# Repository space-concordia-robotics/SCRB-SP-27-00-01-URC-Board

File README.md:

# SCRB-SP-27-00-01
Science Payload URC Extension Board

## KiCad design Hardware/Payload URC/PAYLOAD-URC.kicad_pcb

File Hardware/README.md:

Hardware design for Science Payload URC Extension board

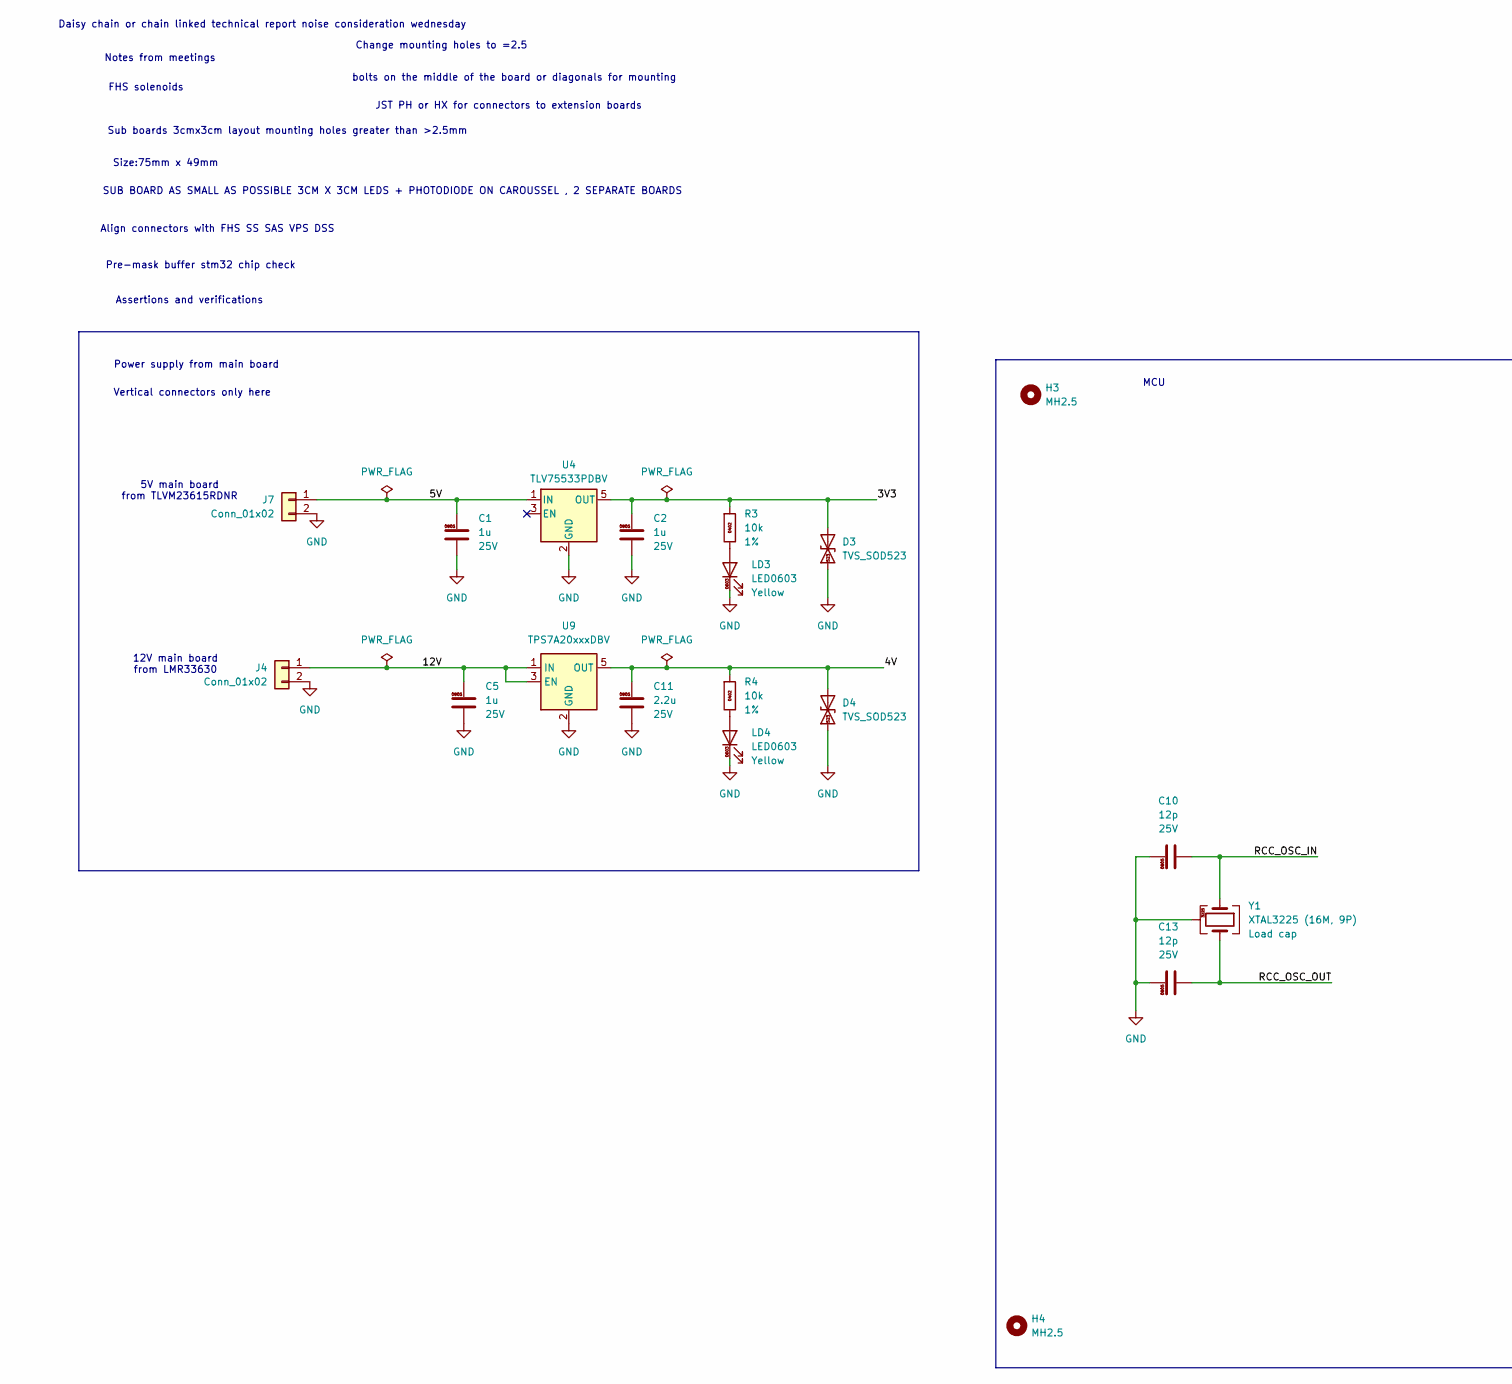
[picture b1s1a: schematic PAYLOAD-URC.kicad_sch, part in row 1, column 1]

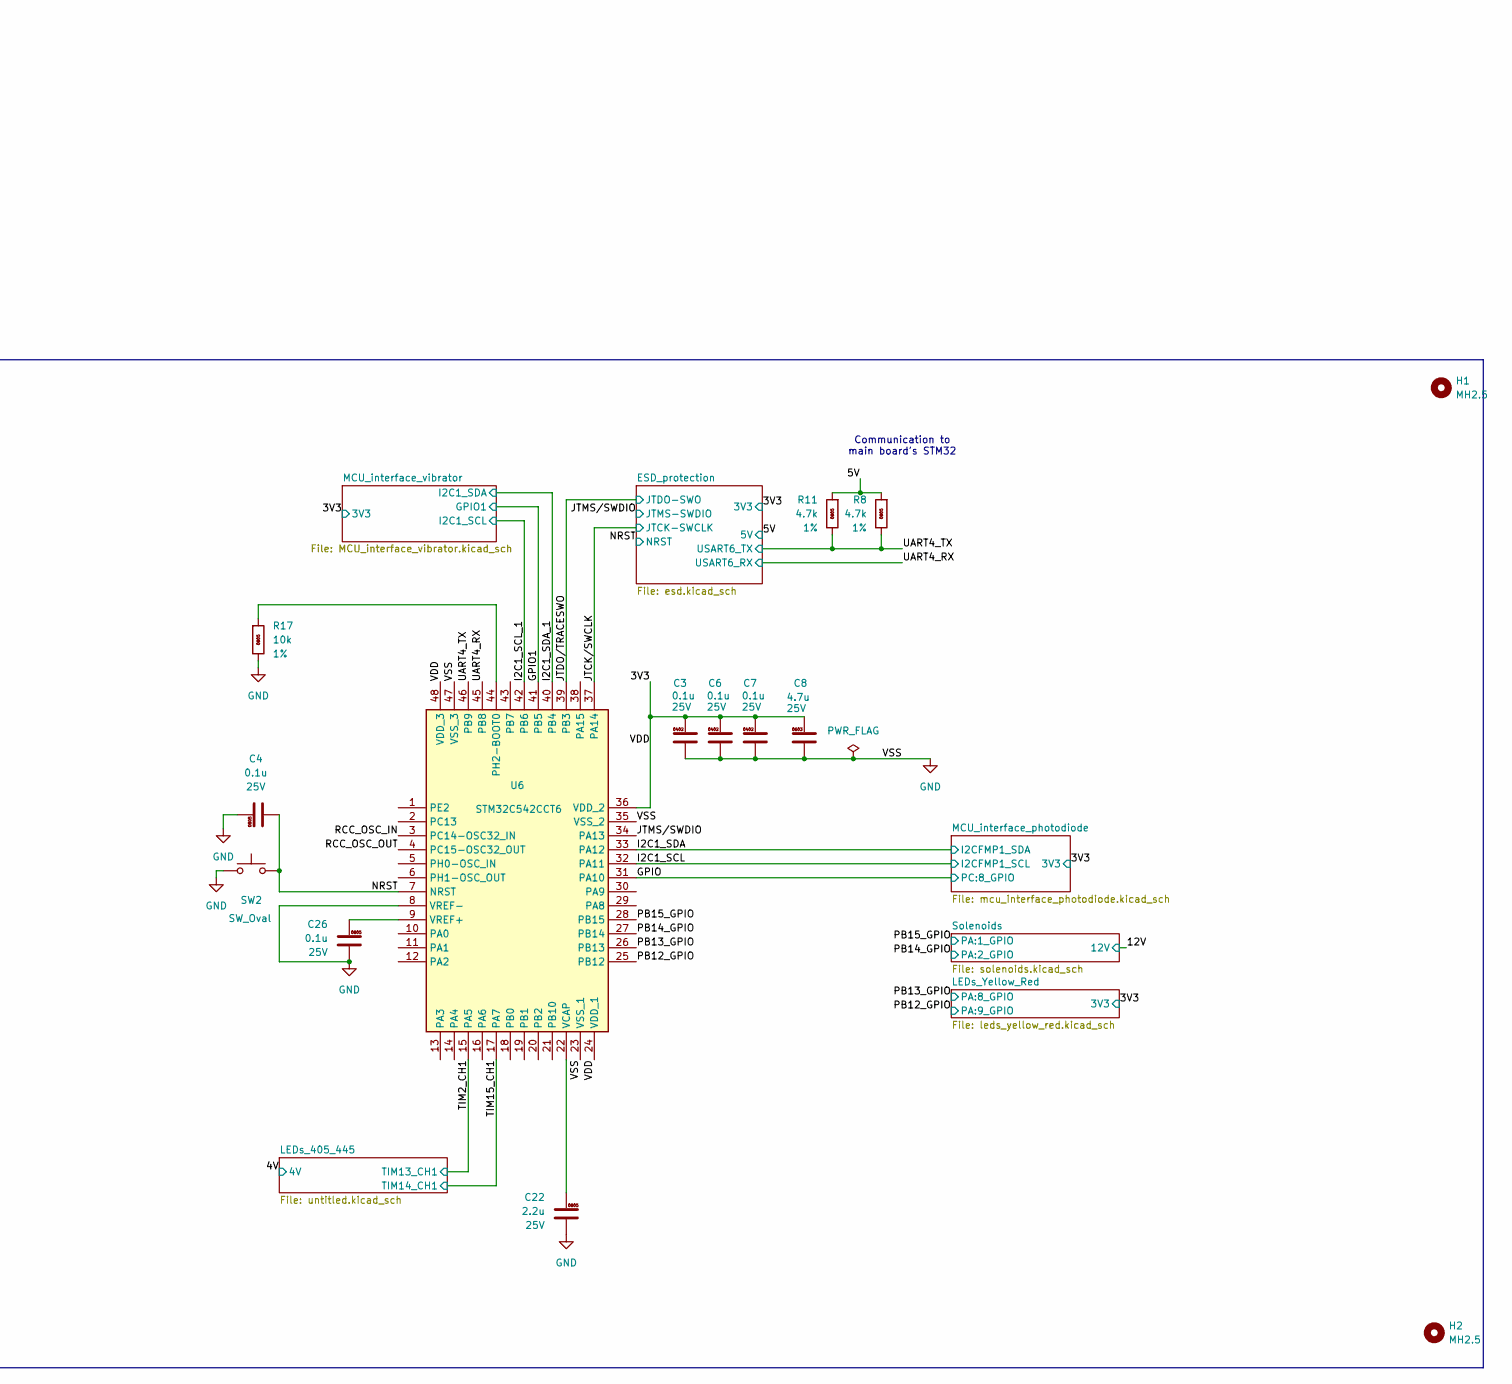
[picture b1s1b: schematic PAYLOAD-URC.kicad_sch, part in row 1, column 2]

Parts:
C1, C2, C5: 1u; C0805; Voltage 25V
C3, C6, C7: 0.1u; C0402; Voltage 25V
C4, C26: 0.1u; C0805; Voltage 25V
C8: 4.7u; C0603; Voltage 25V
C10, C13: 12p; C0805; Voltage 25V
C11, C22: 2.2u; C0805; Voltage 25V
D3, D4: TVS_SOD523; SOD-523
H1, H2, H3, H4: MH2.5; MountingHole_3mm_Pad_TopBottom
J4, J7: Conn_01x02; Molex_Micro-Fit_3.0_43650-0215_1x02_P3.00mm_Vertical
LD3, LD4: LED0603
R3, R4: 10k; R0402
R8, R11: 4.7k; R0805
R17: 10k; R0805
SW2: SW_Oval; SW_C2888430
U4: TLV75533PDBV; SOT-23-5
U6: STM32C542CCT6; LQFP-48_7x7mm_P0.5mm; Manufacturer_Part_Number STM32C542CCT6
U9: TPS7A20xxxDBV; SOT-23-5
Y1: XTAL3225 (16M, 9P); SMD3225

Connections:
/3V3: C2.1, C3.1, C6.1, C7.1, C8.1, D3.2 (A2), R3.1, U4.5 (OUT), U6.24 (VDD_1), U6.36 (VDD_2), U6.48 (VDD_3); also elsewhere on the board
/4V: C11.1, D4.2 (A2), R4.1, U9.5 (OUT); also elsewhere on the board
/5V: C1.1, J7.1, R8.1, R11.1, U4.1 (IN); also elsewhere on the board
/12V: C5.1, J4.1, U9.1 (IN), U9.3 (EN); also elsewhere on the board
/GPIO: U6.31 (PA10); also elsewhere on the board
/GPIO1: U6.41 (PB5)
/I2C1_SCL: U6.32 (PA11); also elsewhere on the board
/I2C1_SCL_1: U6.42 (PB6); also elsewhere on the board
/I2C1_SDA: U6.33 (PA12); also elsewhere on the board
/I2C1_SDA_1: U6.40 (PB4); also elsewhere on the board
/JTCK/SWCLK: U6.37 (PA14); also elsewhere on the board
/JTDO/TRACESWO: U6.39 (PB3)
/JTMS/SWDIO: U6.34 (PA13); also elsewhere on the board
/NRST: C4.2, SW2.2, U6.7 (NRST)
/PB12_GPIO: U6.25 (PB12); also elsewhere on the board
/PB13_GPIO: U6.26 (PB13); also elsewhere on the board
/PB14_GPIO: U6.27 (PB14); also elsewhere on the board
/PB15_GPIO: U6.28 (PB15); also elsewhere on the board
/RCC_OSC_IN: C10.2, U6.3 (PC14-OSC32_IN), Y1.1
/RCC_OSC_OUT: C13.2, U6.4 (PC15-OSC32_OUT), Y1.3
/TIM2_CH1: U6.15 (PA5); also elsewhere on the board
/TIM15_CH1: U6.17 (PA7); also elsewhere on the board
/UART4_RX: U6.45 (PB8); also elsewhere on the board
/UART4_TX: R8.2, R11.2, U6.46 (PB9); also elsewhere on the board
GND: C1.2, C2.2, C3.2, C4.1, C5.2, C6.2, C7.2, C8.2, C10.1, C11.2, C13.1, C22.2, C26.2, D3.1 (A1), D4.1 (A1), J4.2, J7.2, LD3.1 (K), LD4.1 (K), R17.2, SW2.1, U4.2 (GND), U6.8 (VREF-), U6.23 (VSS_1), U6.35 (VSS_2), U6.47 (VSS_3), U9.2 (GND), Y1.2, Y1.4; also elsewhere on the board
unnamed: LD3.2 (A), R3.2
unnamed: LD4.2 (A), R4.2
unnamed: R17.1, U6.44 (PH2-BOOT0)
unnamed: C22.1, U6.22 (VCAP)
unnamed: C26.1, U6.9 (VREF+)

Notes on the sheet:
12V main board from LMR33630
Assertions and verifications
Change mounting holes to =2.5
Communication to main board's STM32
FHS solenoids
Size:75mm x 49mm
Notes from meetings
JST PH or HX for connectors to extension boards
Daisy chain or chain linked technical report noise consideration wednesday
Power supply from main board
SUB BOARD AS SMALL AS POSSIBLE 3CM X 3CM LEDS + PHOTODIODE ON CAROUSSEL , 2 SEPARATE BOARDS
bolts on the middle of the board or diagonals for mounting
Align connectors with FHS SS SAS VPS DSS
Sub boards 3cmx3cm layout mounting holes greater than >2.5mm
MCU
Pre-mask buffer stm32 chip check
5V main board from TLVM23615RDNR
Vertical connectors only here

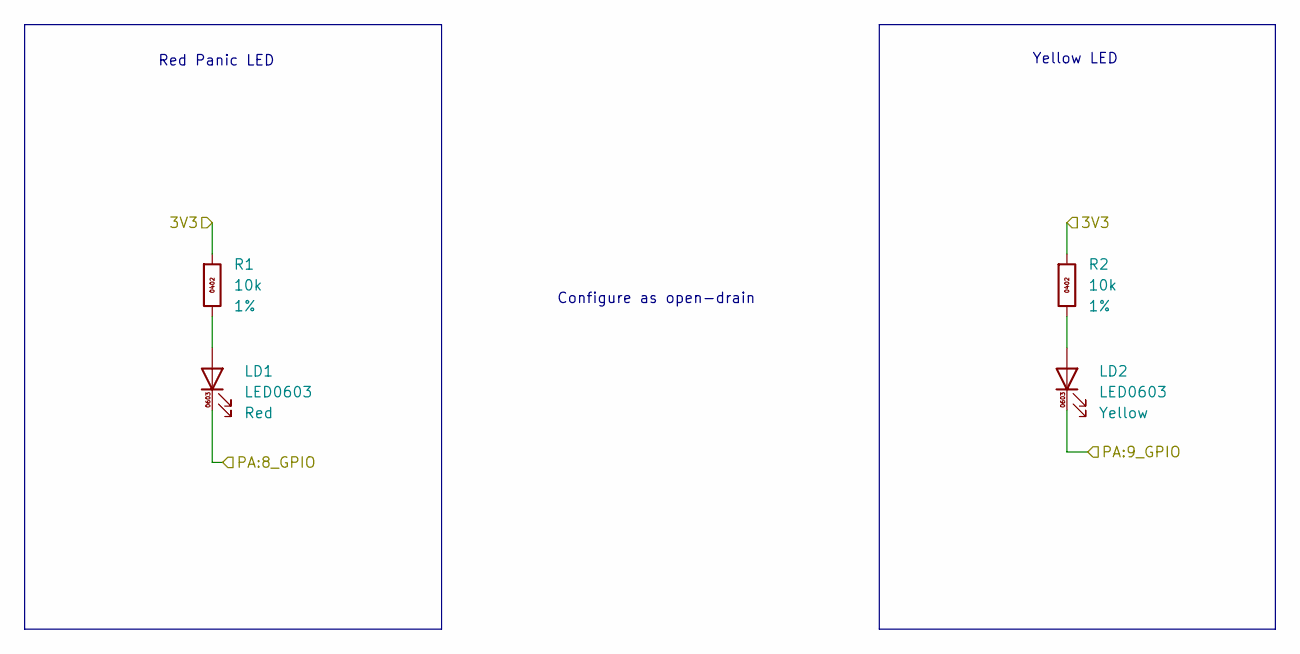
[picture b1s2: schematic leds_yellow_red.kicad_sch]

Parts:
LD1, LD2: LED0603
R1, R2: 10k; R0402

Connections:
/3V3: R1.1, R2.1; also elsewhere on the board
/PB12_GPIO: LD2.1 (K); also elsewhere on the board
/PB13_GPIO: LD1.1 (K); also elsewhere on the board
unnamed: LD1.2 (A), R1.2
unnamed: LD2.2 (A), R2.2

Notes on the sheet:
Red Panic LED
Configure as open-drain
Yellow LED

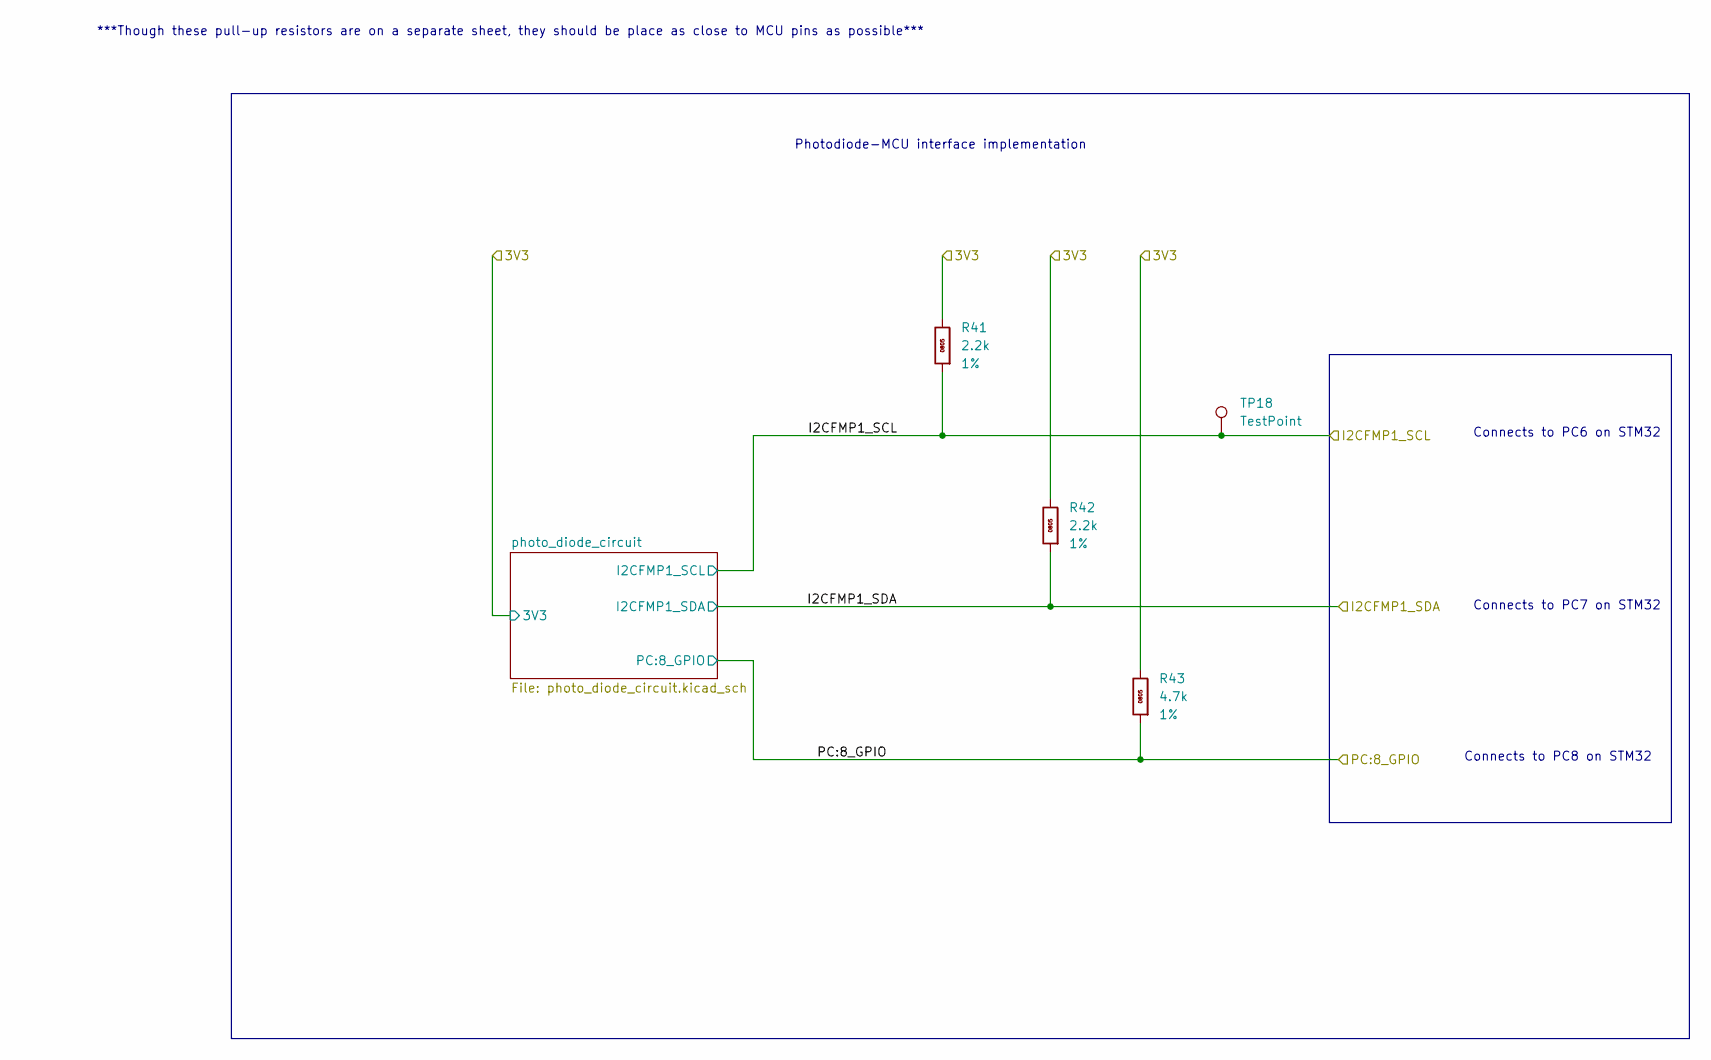
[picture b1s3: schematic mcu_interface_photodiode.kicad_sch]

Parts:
R41, R42: 2.2k; R0805
R43: 4.7k; R0805
TP18: TestPoint; TestPoint_Loop_D2.60mm_Drill1.6mm_Beaded

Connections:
/3V3: R41.2, R42.2, R43.2; also elsewhere on the board
/GPIO: R43.1; also elsewhere on the board
/I2C1_SCL: R41.1, TP18.1 (1_1); also elsewhere on the board
/I2C1_SDA: R42.1; also elsewhere on the board

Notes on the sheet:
***Though these pull-up resistors are on a separate sheet, they should be place as close to MCU pins as possible***
Photodiode-MCU interface implementation
Connects to PC7 on STM32
Connects to PC6 on STM32
Connects to PC8 on STM32

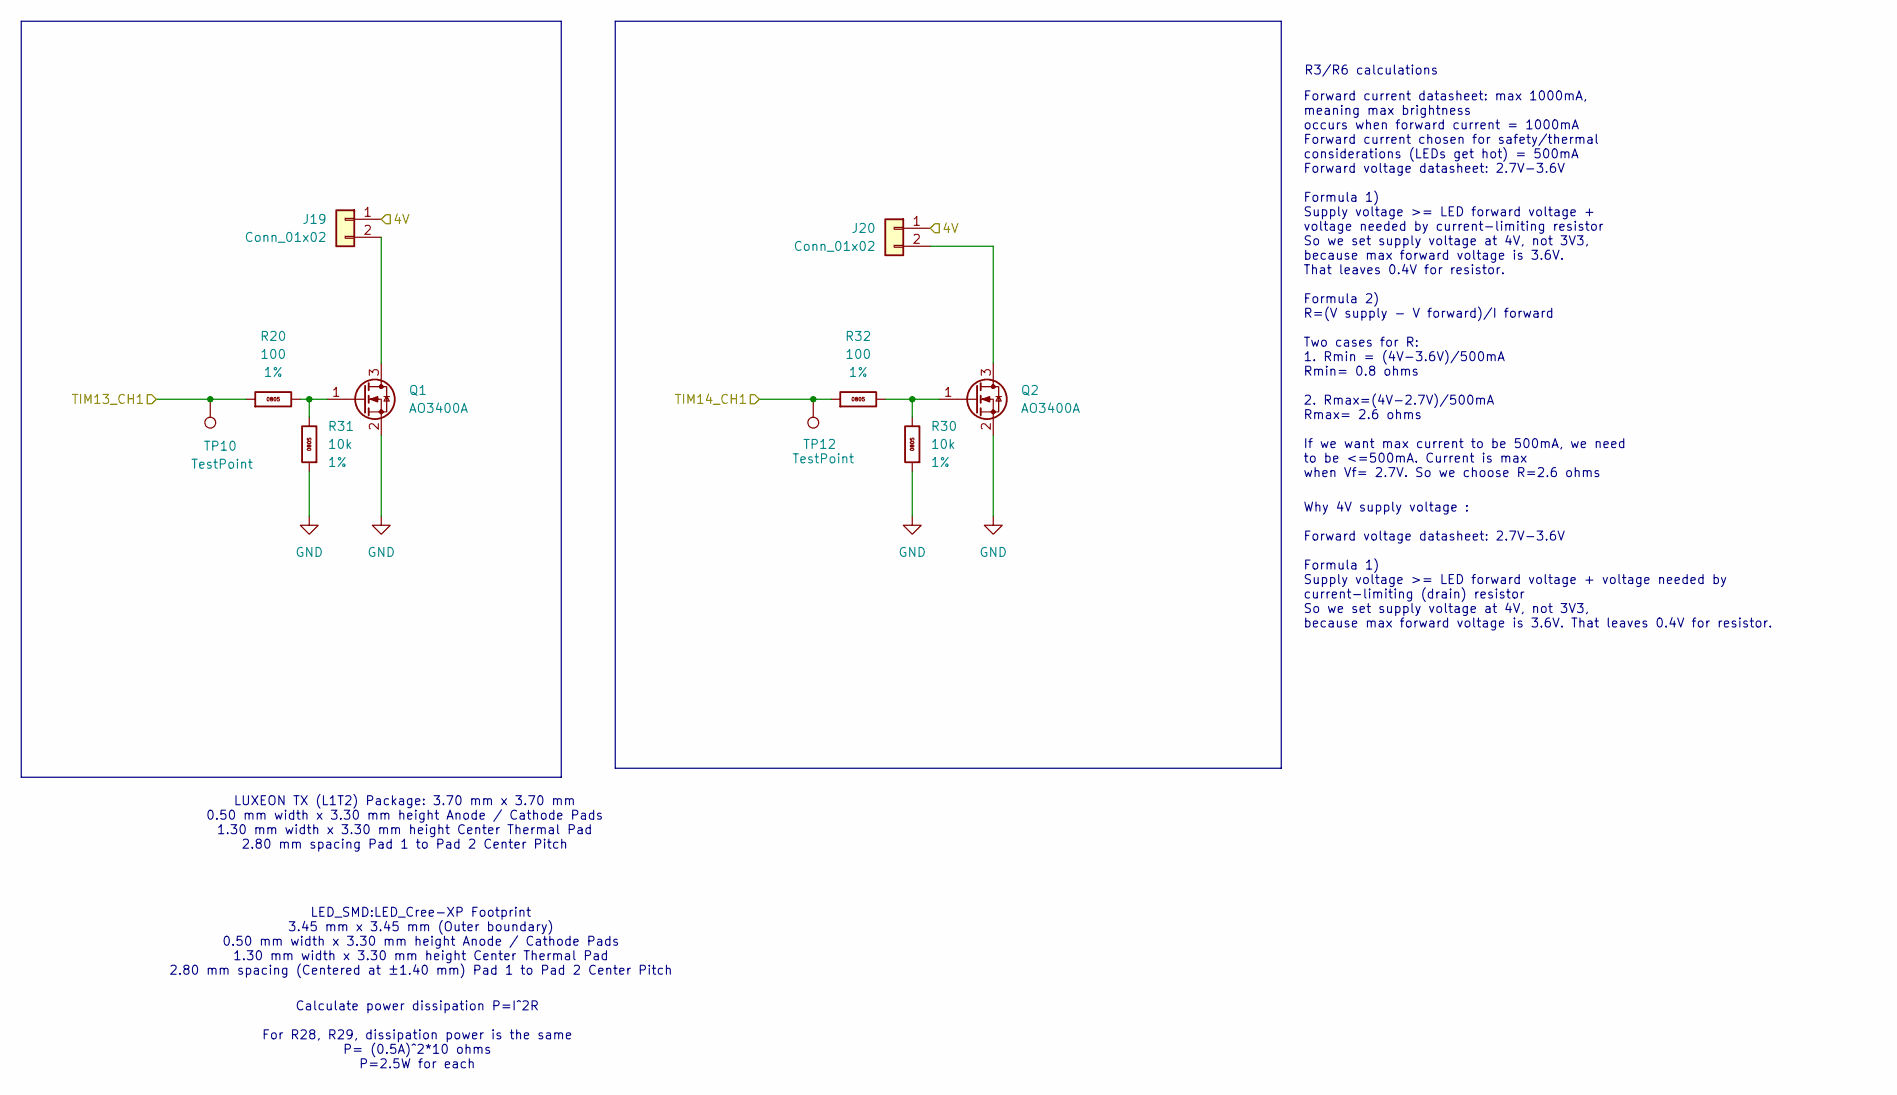
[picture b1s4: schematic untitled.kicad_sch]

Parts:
J19, J20: Conn_01x02; JST-GH-SM04B-GHS-TB
Q1, Q2: AO3400A; SOT-23
R20, R32: 100; R0805
R30, R31: 10k; R0805
TP10, TP12: TestPoint; TestPoint_Loop_D2.60mm_Drill1.6mm_Beaded

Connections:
/4V: J19.1, J20.1; also elsewhere on the board
/TIM2_CH1: R20.1, TP10.1 (1_1); also elsewhere on the board
/TIM15_CH1: R32.1, TP12.1 (1_1); also elsewhere on the board
GND: Q1.2 (S), Q2.2 (S), R30.1, R31.1; also elsewhere on the board
unnamed: J19.2, Q1.3 (D)
unnamed: J20.2, Q2.3 (D)
unnamed: Q1.1 (G), R20.2, R31.2
unnamed: Q2.1 (G), R30.2, R32.2

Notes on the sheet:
LUXEON TX (L1T2) Package: 3.70 mm x 3.70 mm 0.50 mm width x 3.30 mm height Anode / Cathode Pads 1.30 mm width x 3.30 mm height Center Thermal Pad 2.80 mm spacing Pad 1 to Pad 2 Center Pitch
R3/R6 calculations
LED_SMD:LED_Cree-XP Footprint 3.45 mm x 3.45 mm (Outer boundary) 0.50 mm width x 3.30 mm height Anode / Cathode Pads 1.30 mm width x 3.30 mm height Center Thermal Pad 2.80 mm spacing (Centered at ±1.40 mm) Pad 1 to Pad 2 Center Pitch
Forward current datasheet: max 1000mA, meaning max brightness occurs when forward current = 1000mA Forward current chosen for safety/thermal considerations (LEDs get hot) = 500mA Forward voltage datasheet: 2.7V-3.6V Formula 1) Supply voltage >= LED forward voltage + voltage needed by current-limiti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
Why 4V supply voltage : Forward voltage datasheet: 2.7V-3.6V Formula 1) Supply voltage >= LED forward voltage + voltage needed by current-limiting (drain) resistor So we set supply voltage at 4V, not 3V3, because max forward voltage is 3.6V. That leaves 0.4V for resistor.
Calculate power dissipation P=I^2R For R28, R29, dissipation power is the same P= (0.5A)^2*10 ohms P=2.5W for each

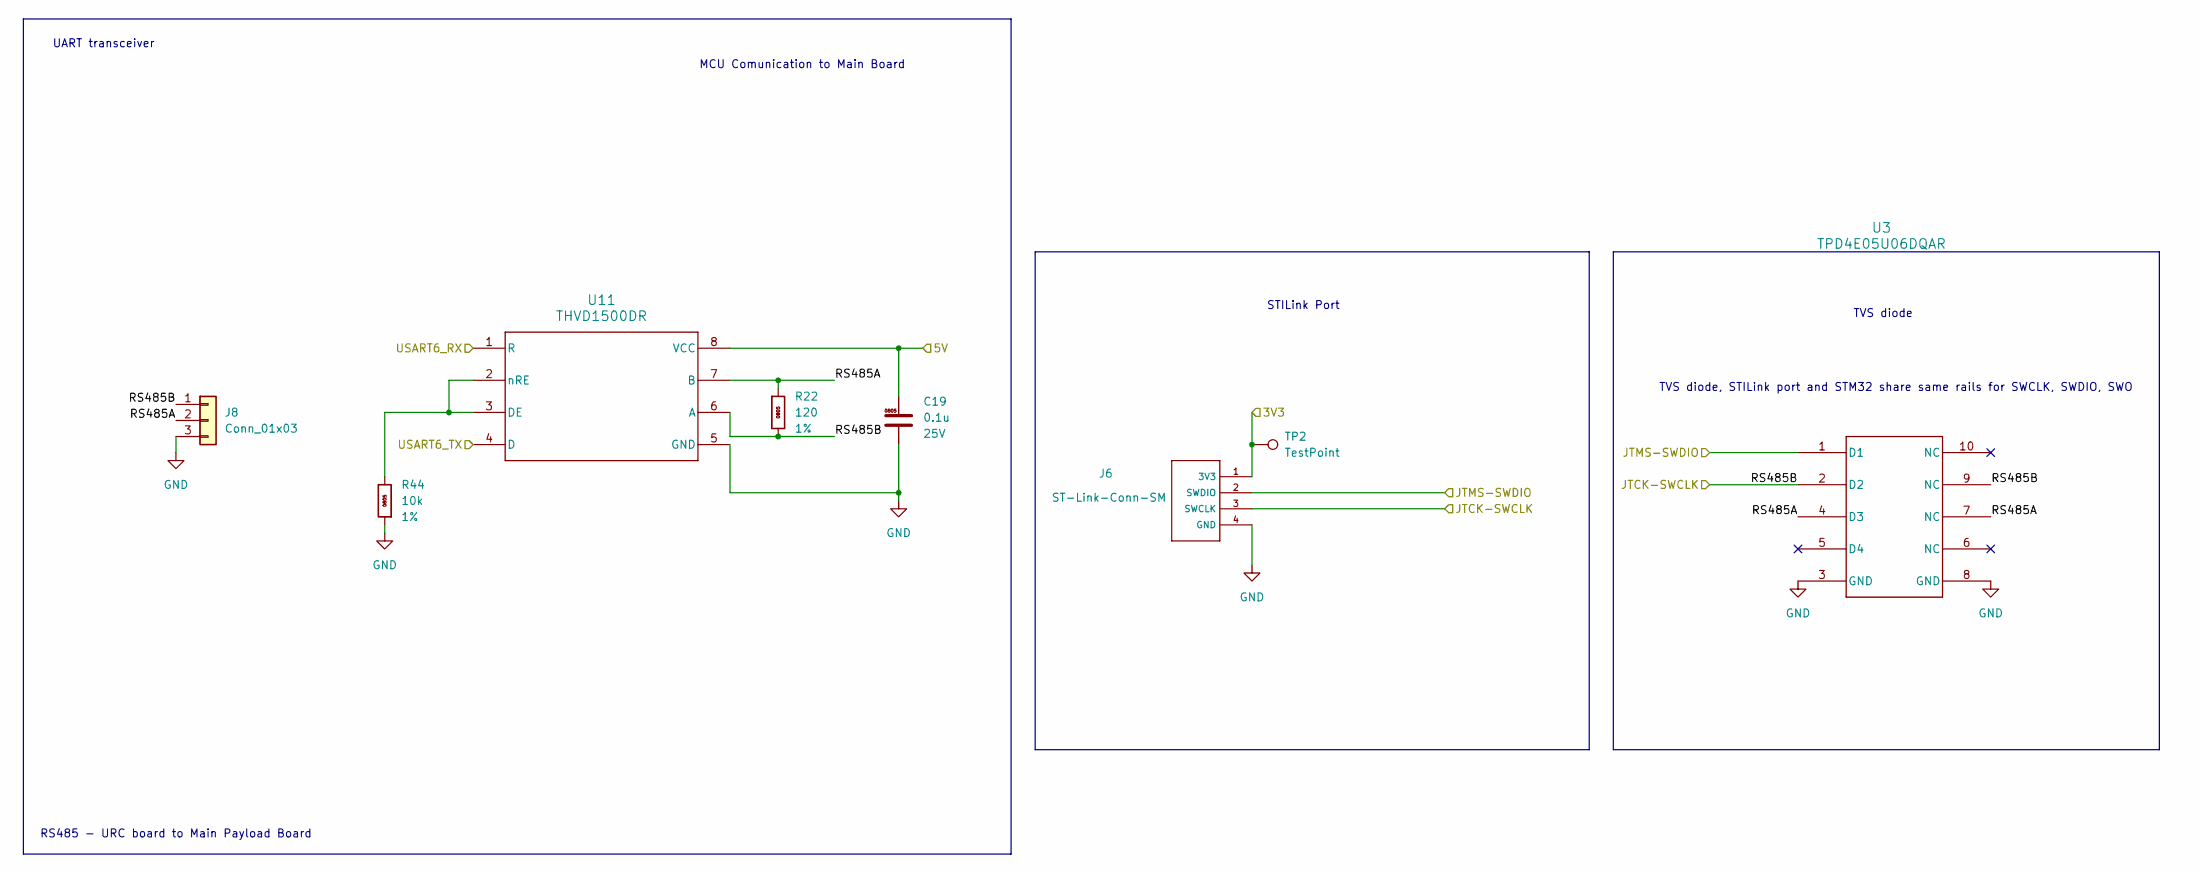
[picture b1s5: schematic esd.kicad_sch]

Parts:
C19: 0.1u; C0805; Voltage 25V
J6: ST-Link-Conn-SM; JST_PH_B4B-PH-SM4-TB_1x04-1MP_P2.00mm_Vertical
J8: Conn_01x03; Hirose_DF57H-3P-1.2V_1x03_P1.2mm_Socket
R22: 120; R0805
R44: 10k; R0805
TP2: TestPoint; TestPoint_Loop_D2.60mm_Drill1.6mm_Beaded
U3: TPD4E05U06DQAR; DQA0010A
U11: THVD1500DR; D0008A

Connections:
/3V3: J6.1 (3V3), TP2.1 (1_1); also elsewhere on the board
/5V: C19.1, U11.8 (VCC); also elsewhere on the board
/ESD_protection/RS485A: J8.2, R22.1, U3.4 (D3), U3.7 (NC), U11.7 (B)
/JTCK/SWCLK: J6.3 (SWCLK), J8.1, R22.2, U3.2 (D2), U3.9 (NC), U11.6 (A); also elsewhere on the board
/JTMS/SWDIO: J6.2 (SWDIO), U3.1 (D1); also elsewhere on the board
/UART4_RX: U11.1 (R); also elsewhere on the board
/UART4_TX: U11.4 (D); also elsewhere on the board
GND: C19.2, J6.4 (GND), J8.3, R44.1, U3.3 (GND), U3.8 (GND), U11.5 (GND); also elsewhere on the board
unnamed: R44.2, U11.2 (nRE), U11.3 (DE)

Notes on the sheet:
UART transceiver
MCU Comunication to Main Board
TVS diode
STILink Port
RS485 - URC board to Main Payload Board
TVS diode, STILink port and STM32 share same rails for SWCLK, SWDIO, SWO

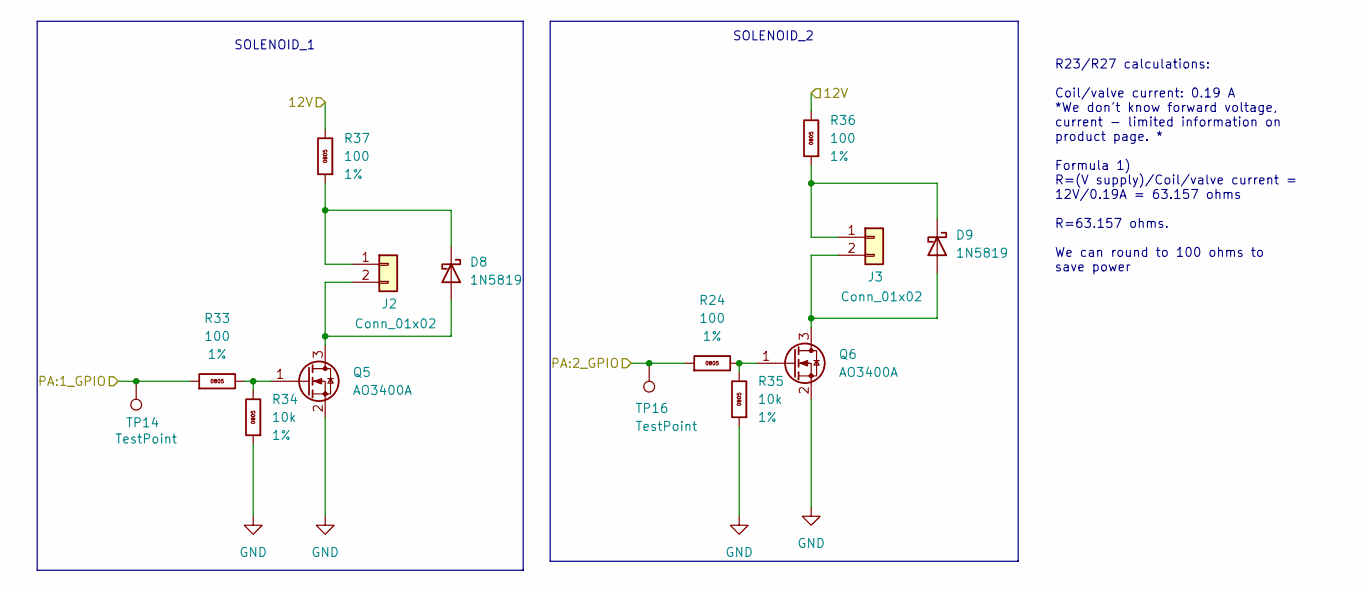
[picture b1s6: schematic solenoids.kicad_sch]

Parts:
D8, D9: 1N5819; D_DO-41_SOD81_P10.16mm_Horizontal
J2, J3: Conn_01x02; JST_PH_S2B-PH-K_1x02_P2.00mm_Horizontal
Q5, Q6: AO3400A; SOT-23
R24, R33, R36, R37: 100; R0805
R34, R35: 10k; R0805
TP14, TP16: TestPoint; TestPoint_Loop_D2.60mm_Drill1.6mm_Beaded

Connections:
/12V: R36.2, R37.2; also elsewhere on the board
/PB14_GPIO: R24.1, TP16.1 (1_1); also elsewhere on the board
/PB15_GPIO: R33.1, TP14.1 (1_1); also elsewhere on the board
GND: Q5.2 (S), Q6.2 (S), R34.1, R35.1; also elsewhere on the board
unnamed: D8.2 (A), J2.2, Q5.3 (D)
unnamed: D8.1 (K), J2.1, R37.1
unnamed: D9.2 (A), J3.2, Q6.3 (D)
unnamed: D9.1 (K), J3.1, R36.1
unnamed: Q5.1 (G), R33.2, R34.2
unnamed: Q6.1 (G), R24.2, R35.2

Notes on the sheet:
R23/R27 calculations: Coil/valve current: 0.19 A *We don't know forward voltage, current - limited information on product page. * Formula 1) R=(V supply)/Coil/valve current = 12V/0.19A = 63.157 ohms R=63.157 ohms. We can round to 100 ohms to save power
SOLENOID_1
SOLENOID_2

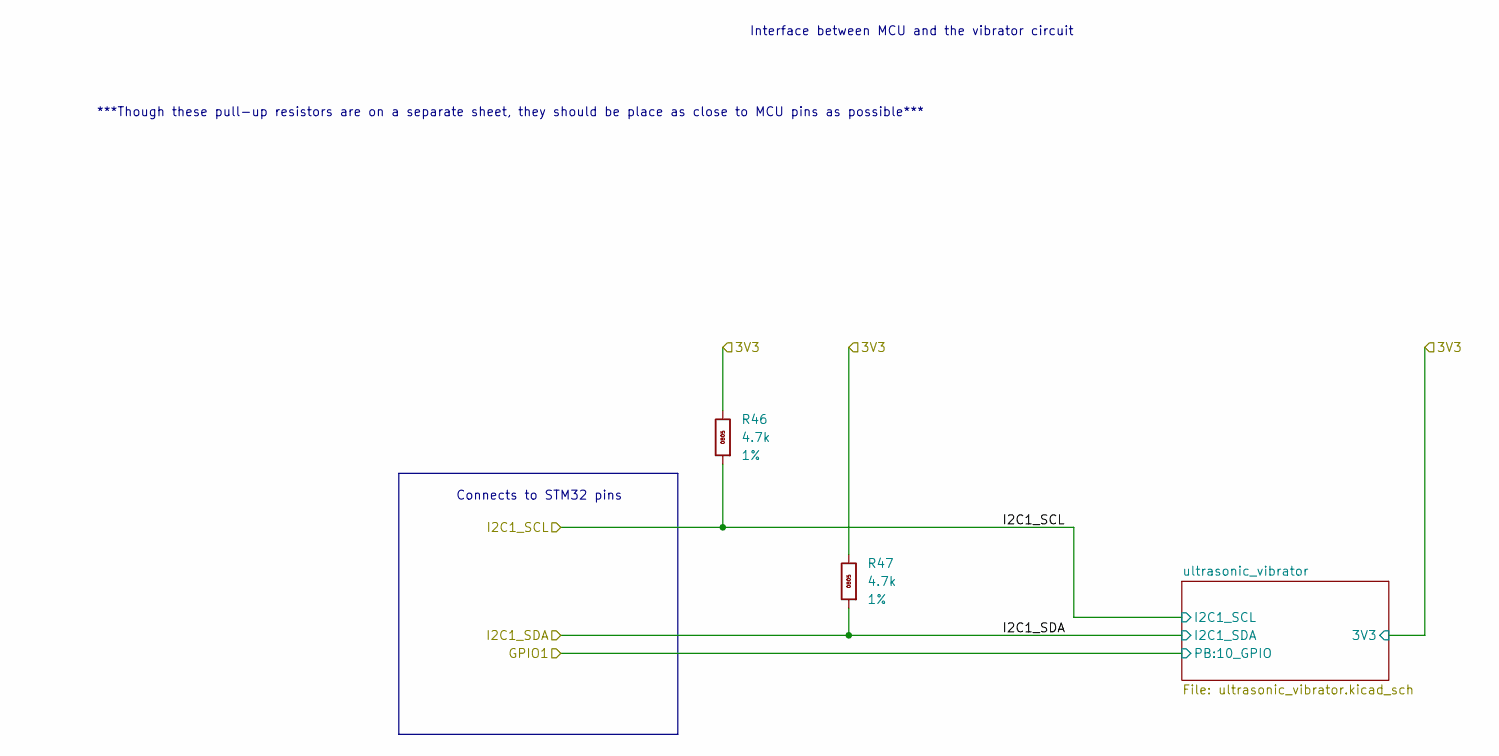
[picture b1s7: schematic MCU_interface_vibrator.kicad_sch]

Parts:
R46, R47: 4.7k; R0805

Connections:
/3V3: R46.2, R47.2; also elsewhere on the board
/I2C1_SCL_1: R46.1; also elsewhere on the board
/I2C1_SDA_1: R47.1; also elsewhere on the board

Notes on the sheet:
***Though these pull-up resistors are on a separate sheet, they should be place as close to MCU pins as possible***
Interface between MCU and the vibrator circuit
Connects to STM32 pins

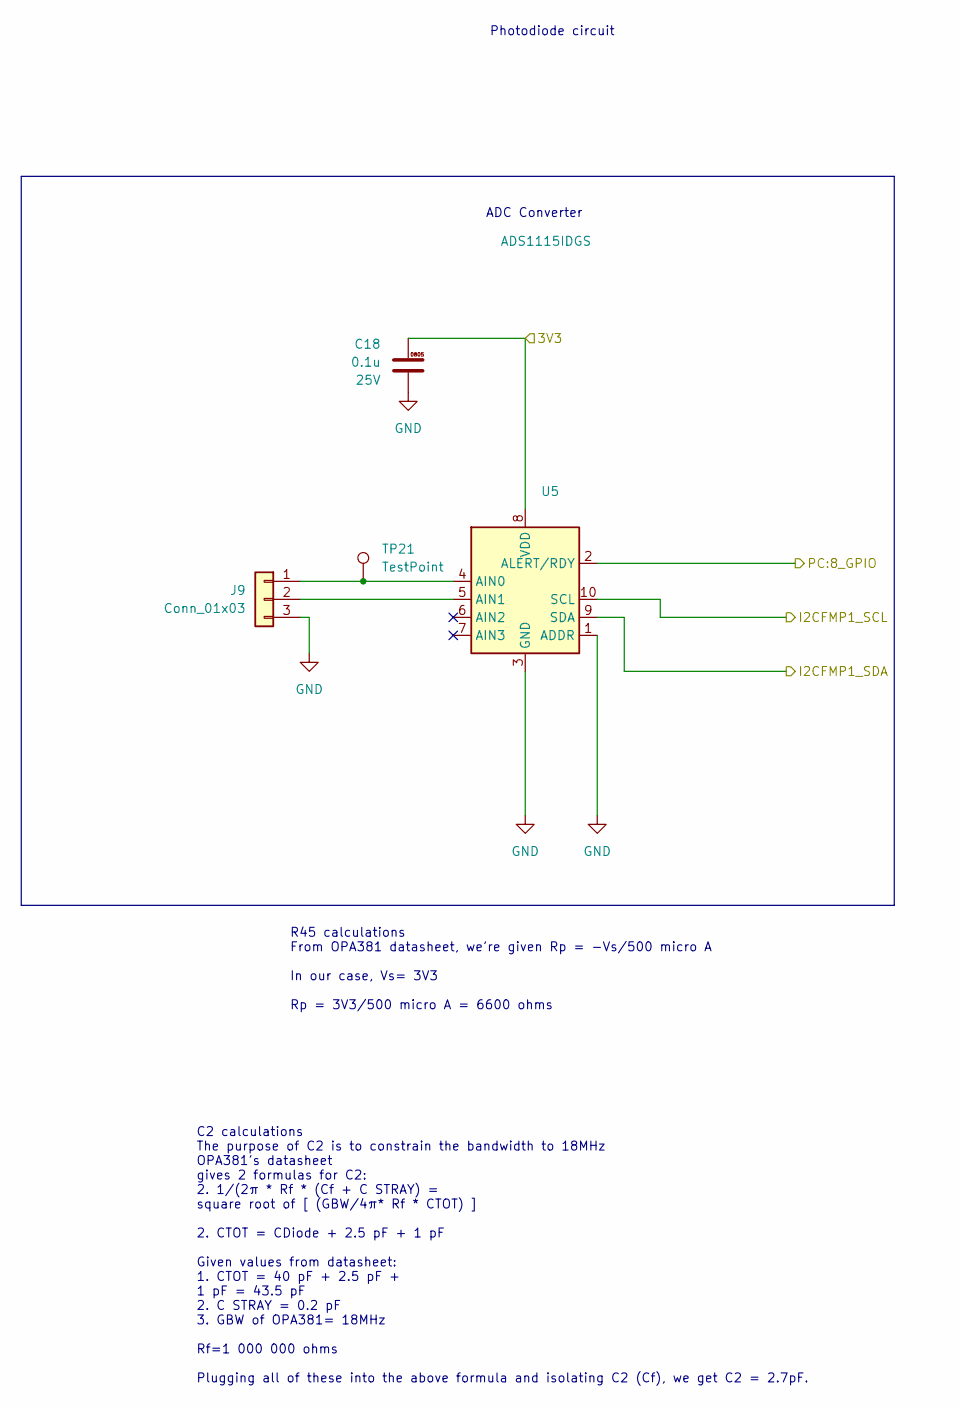
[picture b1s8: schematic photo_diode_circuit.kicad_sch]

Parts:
C18: 0.1u; C0805; Voltage 25V
J9: Conn_01x03; Hirose_DF57H-3P-1.2V_1x03_P1.2mm_Socket
TP21: TestPoint; TestPoint_Loop_D2.60mm_Drill1.6mm_Beaded
U5: ADS1115IDGS; TSSOP-10_3x3mm_P0.5mm

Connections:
/3V3: C18.1, U5.8 (VDD); also elsewhere on the board
/GPIO: U5.2 (ALERT/RDY); also elsewhere on the board
/I2C1_SCL: U5.10 (SCL); also elsewhere on the board
/I2C1_SDA: U5.9 (SDA); also elsewhere on the board
GND: C18.2, J9.3, U5.1 (ADDR), U5.3 (GND); also elsewhere on the board
unnamed: J9.1, TP21.1 (1_1), U5.4 (AIN0)
unnamed: J9.2, U5.5 (AIN1)

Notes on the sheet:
C2 calculations The purpose of C2 is to constrain the bandwidth to 18MHz OPA381's datasheet gives 2 formulas for C2: 2. 1/(2π * Rf * (Cf + C STRAY) = square root of [ (GBW/4π* Rf * CTOT) ] 2. CTOT = CDiode + 2.5 pF + 1 pF Given values from datasheet: 1. CTOT = 40 pF + 2.5 pF + 1 pF = 43.5 pF 2. C S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
ADC Converter
R45 calculations From OPA381 datasheet, we're given Rp = -Vs/500 micro A In our case, Vs= 3V3 Rp = 3V3/500 micro A = 6600 ohms
Photodiode circuit

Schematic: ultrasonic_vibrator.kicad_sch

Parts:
C20, C21: 1u; C0805; Voltage 25V
J1: VG2080001H; JST-GH-SM04B-GHS-TB
TP35: TestPoint; TestPoint_Loop_D2.60mm_Drill1.6mm_Beaded
U1: DRV2605LDGS; TSSOP-10_3x3mm_P0.5mm

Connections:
/3V3: C20.2, U1.10 (VDD); also elsewhere on the board
/I2C1_SCL_1: U1.2 (SCL); also elsewhere on the board
/I2C1_SDA_1: TP35.1 (1_1), U1.3 (SDA); also elsewhere on the board
/MCU_interface_vibrator/ultrasonic_vibrator/GPIO1: U1.5 (EN)
GND: C20.1, C21.2, U1.4 (IN/TRIG), U1.8 (GND); also elsewhere on the board
unnamed: J1.1, U1.7 (OUT+)
unnamed: J1.2, U1.9 (OUT-)
unnamed: C21.1, U1.1 (REG)

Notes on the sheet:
Connects to STM32 pins
Motor connector
Ultrasonic vibrator circuit
Ultrasonic vibrator
Driver

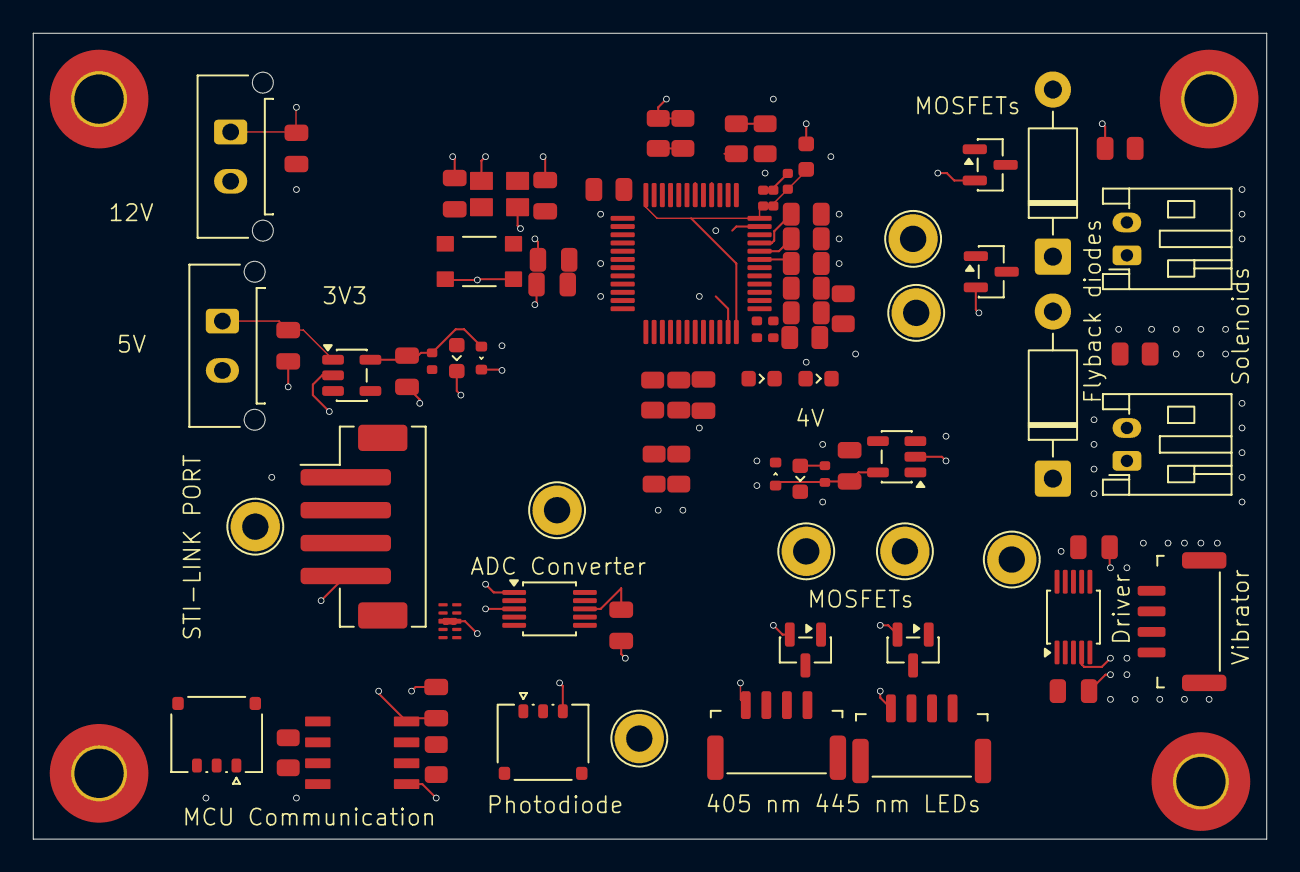
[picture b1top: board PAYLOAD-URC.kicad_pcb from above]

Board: 4 copper layers, 75.0 x 49.0 mm, 84 parts (0 on the bottom side), 47 nets.

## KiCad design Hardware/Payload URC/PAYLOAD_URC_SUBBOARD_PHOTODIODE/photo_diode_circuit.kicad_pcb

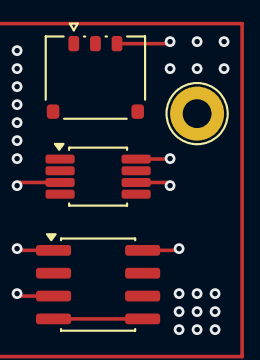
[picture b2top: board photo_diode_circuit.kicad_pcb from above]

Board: 4 copper layers, 4 parts (0 on the bottom side), 3 nets.

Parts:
J8: Conn_01x03; Hirose_DF57H-3P-1.2V_1x03_P1.2mm_Socket
TP21: TestPoint; TestPoint_Loop_D2.60mm_Drill1.6mm_Beaded
U11: THS4536; VSSOP-8_3x3mm_P0.65mm
U12: OPT101; SOIC-8_3.9x4.9mm_P1.27mm

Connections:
/3V3: U11.3 (V_{S+}), U11.8 (+), U12.1 (V+)
GND: J8.3, U11.6 (V_{S-}), U12.3 (ENABLE), U12.8 (V-)
unnamed: U12.4 (-), U12.5
